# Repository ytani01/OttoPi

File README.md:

# OttoPi: Otto DIY like biped robot for Raspberry Pi

see [github pages](https://ytani01.github.io/OttoPi/)

## Power ON/OFF Button

### Power ON button

GPIO 3 -> SW -> GND

### Shutdown button

GPIO 4 -> SW -> GND
GPIO 21 -> R(1K ohm) -> LED -> GND

```
dtoverlay=gpio-shutdown,gpio_pin=4
dtoverlay=gpio-poweroff,gpiopin=21,active_low=1
```

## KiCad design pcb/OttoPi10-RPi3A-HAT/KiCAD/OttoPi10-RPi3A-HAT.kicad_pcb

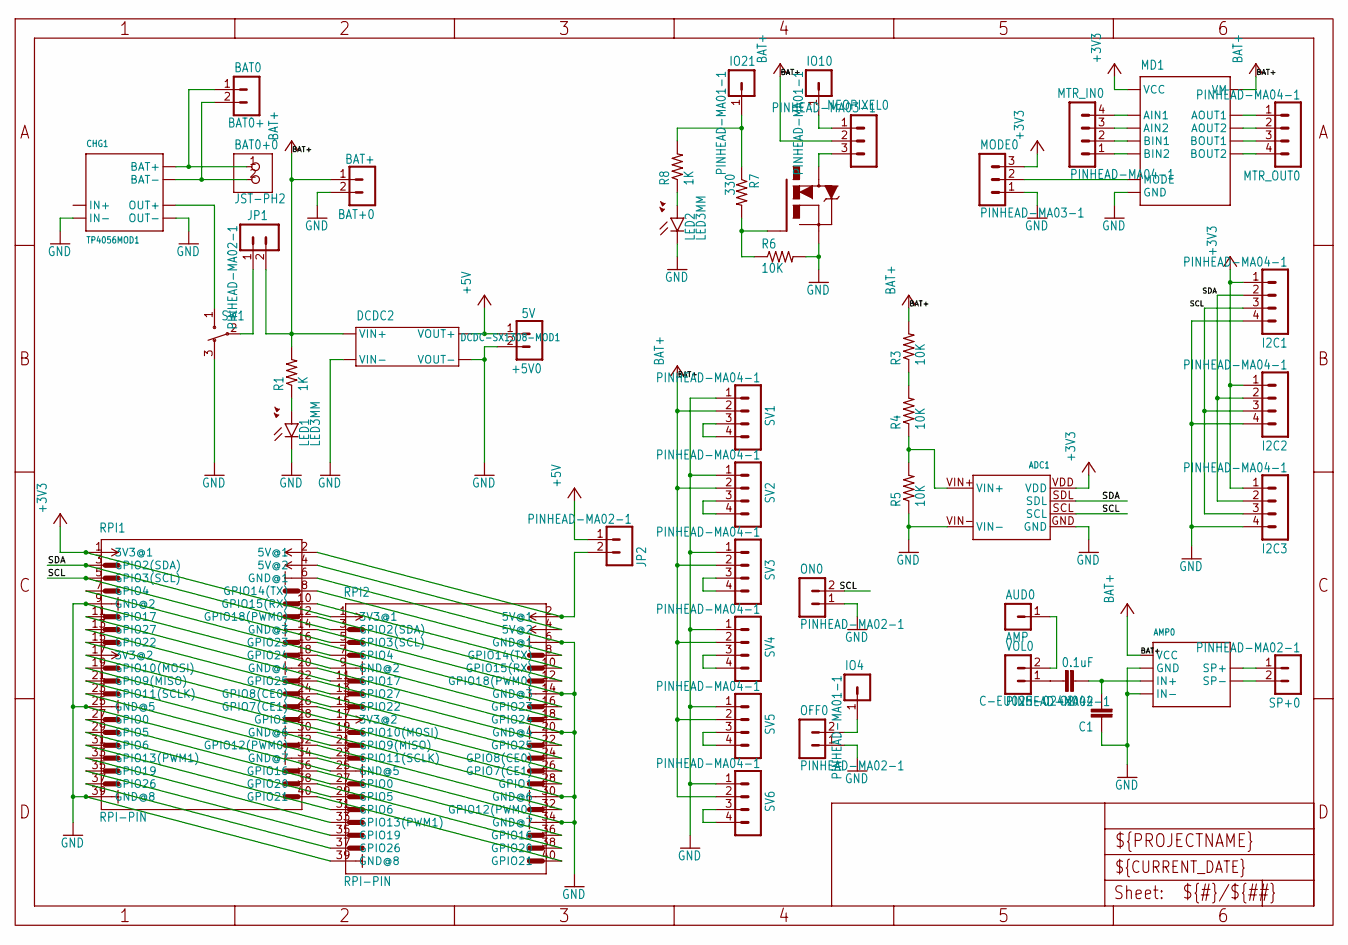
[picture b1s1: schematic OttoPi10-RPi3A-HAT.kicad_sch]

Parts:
+5V0: 5V; PINHEAD-MA02-1
ADC1: MCP3425MOD
AMP0: AMP; PAM8012MOD-A
AUD0: AMP; PINHEAD-MA01-1
BAT0: BAT0+; PINHEAD-MA02-1
BAT0+0: JST-PH2
BAT+0: BAT+; PINHEAD-MA02-1
C1: C-EU025-024X044; C025-024X044
C2: 0.1uF; C025-024X044
CHG1: TP4056MOD1
DCDC2: DCDC-SX1308-MOD1
I2C1, I2C2, I2C3: PINHEAD-MA04-1
IO4, IO10, IO21: PINHEAD-MA01-1
JP1, JP2: PINHEAD-MA02-1
LED1, LED2: LED3MM
MD1: DRV8835MOD
MODE0: PINHEAD-MA03-1
MTR_IN0: PINHEAD-MA04-1
MTR_OUT0: PINHEAD-MA04-1
NEOPIXEL0: PINHEAD-MA03-1
OFF0: PINHEAD-MA02-1
ON0: PINHEAD-MA02-1
Q1: 2SK4017; MOSFET-1
R1, R8: 1K; 0204_7
R3, R4, R5, R6: 10K; 0204_7
R7: 330; 0204_7
RPI1, RPI2: RPI-PIN
SP+0: PINHEAD-MA02-1
SV1, SV2, SV3, SV4, SV5, SV6: PINHEAD-MA04-1
SW1: SW3-1
VOL0: PINHEAD-MA02-1

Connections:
+3V3: ADC1.VDD, I2C1.1, I2C2.1, I2C3.1, MD1.VCC, MODE0.3, RPI1.1 (3V3@1), RPI2.1 (3V3@1)
+5V: +5V0.1, DCDC2.VOUT+, JP2.1
AIN1: MD1.AIN1, MTR_IN0.4
AIN2: MD1.AIN2, MTR_IN0.3
AOUT1: MD1.AOUT1, MTR_OUT0.1
AOUT2: MD1.AOUT2, MTR_OUT0.2
AUDIO0: AUD0.1, VOL0.2
AUDIO1: AMP0.IN+, C1.2, C2.1
BAT+: AMP0.V+ (VCC), BAT+0.1, DCDC2.VIN+, JP1.2, MD1.VM, NEOPIXEL0.2, R1.2, R3.2, SV1.2, SV2.2, SV3.2, SV4.2, SV5.2, SV6.2
BAT+0: BAT0.1, BAT0+0.1, CHG1.BAT+
BAT+1: CHG1.OUT+, SW1.1
BAT+2: JP1.1, SW1.2
BAT-0: BAT0.2, BAT0+0.2, CHG1.BAT-
BIN1: MD1.BIN1, MTR_IN0.2
BIN2: MD1.BIN2, MTR_IN0.1
BOUT1: MD1.BOUT1, MTR_OUT0.3
BOUT2: MD1.BOUT2, MTR_OUT0.4
GND: +5V0.2, ADC1.GND, ADC1.VIN-, AMP0.GND, AMP0.IN-, BAT+0.2, C1.1, CHG1.IN-, CHG1.OUT-, DCDC2.VIN-, DCDC2.VOUT-, I2C1.4, I2C2.4, I2C3.4, LED1.K (C), LED2.K (C), MD1.GND, MODE0.1, OFF0.1, ON0.1, Q1.S, R5.1, R6.2, RPI1.6 (GND@1), RPI1.9 (GND@2), RPI1.14 (GND@3), RPI1.20 (GND@4), RPI1.25 (GND@5), RPI1.30 (GND@6), RPI1.34 (GND@7), RPI1.39 (GND@8), RPI2.6 (GND@1), RPI2.9 (GND@2), RPI2.14 (GND@3), RPI2.20 (GND@4), RPI2.25 (GND@5), RPI2.30 (GND@6), RPI2.34 (GND@7), RPI2.39 (GND@8), SV1.1, SV2.1, SV3.1, SV4.1, SV5.1, SV6.1, SW1.3
GPIO10: RPI1.17 (3V3@2), RPI2.17 (3V3@2)
MODE: MD1.MODE, MODE0.2
unnamed: Q1.G, R6.1, R7.2
unnamed: NEOPIXEL0.3, Q1.D
unnamed: LED1.A, R1.1
unnamed: IO21.1, R7.1, R8.2
unnamed: JP2.2, RPI1.2 (5V@1), RPI2.2 (5V@1)
unnamed: RPI1.7 (GPIO4), RPI2.7 (GPIO4)
unnamed: IO10.1, NEOPIXEL0.1
unnamed: RPI1.11 (GPIO17), RPI2.11 (GPIO17)
unnamed: RPI1.13 (GPIO27), RPI2.13 (GPIO27)
unnamed: RPI1.15 (GPIO22), RPI2.15 (GPIO22)
unnamed: RPI1.23 (GPIO11(SCLK)), RPI2.23 (GPIO11(SCLK))
unnamed: RPI1.19 (GPIO10(MOSI)), RPI2.19 (GPIO10(MOSI))
unnamed: RPI1.21 (GPIO9(MISO)), RPI2.21 (GPIO9(MISO))
unnamed: C2.2, VOL0.1
unnamed: RPI1.4 (5V@2), RPI2.4 (5V@2)
unnamed: LED2.A, R8.1
unnamed: RPI1.8 (GPIO14(TX)), RPI2.8 (GPIO14(TX))
unnamed: RPI1.10 (GPIO15(RX)), RPI2.10 (GPIO15(RX))
unnamed: RPI1.12 (GPIO18(PWM0)), RPI2.12 (GPIO18(PWM0))
unnamed: RPI1.16 (GPIO23), RPI2.16 (GPIO23)
unnamed: RPI1.18 (GPIO24), RPI2.18 (GPIO24)
unnamed: RPI1.22 (GPIO25), RPI2.22 (GPIO25)
unnamed: IO4.1, OFF0.2
unnamed: R3.1, R4.2
unnamed: ADC1.VIN+, R4.1, R5.2
unnamed: RPI1.24 (GPIO8(CE0)), RPI2.24 (GPIO8(CE0))
unnamed: RPI1.26 (GPIO7(CE1)), RPI2.26 (GPIO7(CE1))
unnamed: RPI1.27 (GPIO0), RPI2.27 (GPIO0)
unnamed: RPI1.28 (GPIO1), RPI2.28 (GPIO1)
unnamed: RPI1.29 (GPIO5), RPI2.29 (GPIO5)
unnamed: RPI1.31 (GPIO6), RPI2.31 (GPIO6)
unnamed: RPI1.32 (GPIO12(PWM0)), RPI2.32 (GPIO12(PWM0))
unnamed: RPI1.33 (GPIO13(PWM1)), RPI2.33 (GPIO13(PWM1))
unnamed: RPI1.35 (GPIO19), RPI2.35 (GPIO19)
unnamed: RPI1.36 (GPIO16), RPI2.36 (GPIO16)
unnamed: RPI1.37 (GPIO26), RPI2.37 (GPIO26)
unnamed: RPI1.38 (GPIO20), RPI2.38 (GPIO20)
unnamed: RPI1.40 (GPIO21), RPI2.40 (GPIO21)
unnamed: SV2.3, SV2.4
unnamed: SV3.3, SV3.4
unnamed: SV4.3, SV4.4
unnamed: SV1.3, SV1.4
unnamed: SV5.3, SV5.4
unnamed: SV6.3, SV6.4
SCL: ADC1.SCL, I2C1.3, I2C2.3, I2C3.3, ON0.2, RPI1.5 (GPIO3(SCL)), RPI2.5 (GPIO3(SCL))
SDA: ADC1.SDL, I2C1.2, I2C2.2, I2C3.2, RPI1.3 (GPIO2(SDA)), RPI2.3 (GPIO2(SDA))
SP+: AMP0.SP+@1 (SP+), SP+0.1
SP-: AMP0.SP-@1 (SP-), SP+0.2

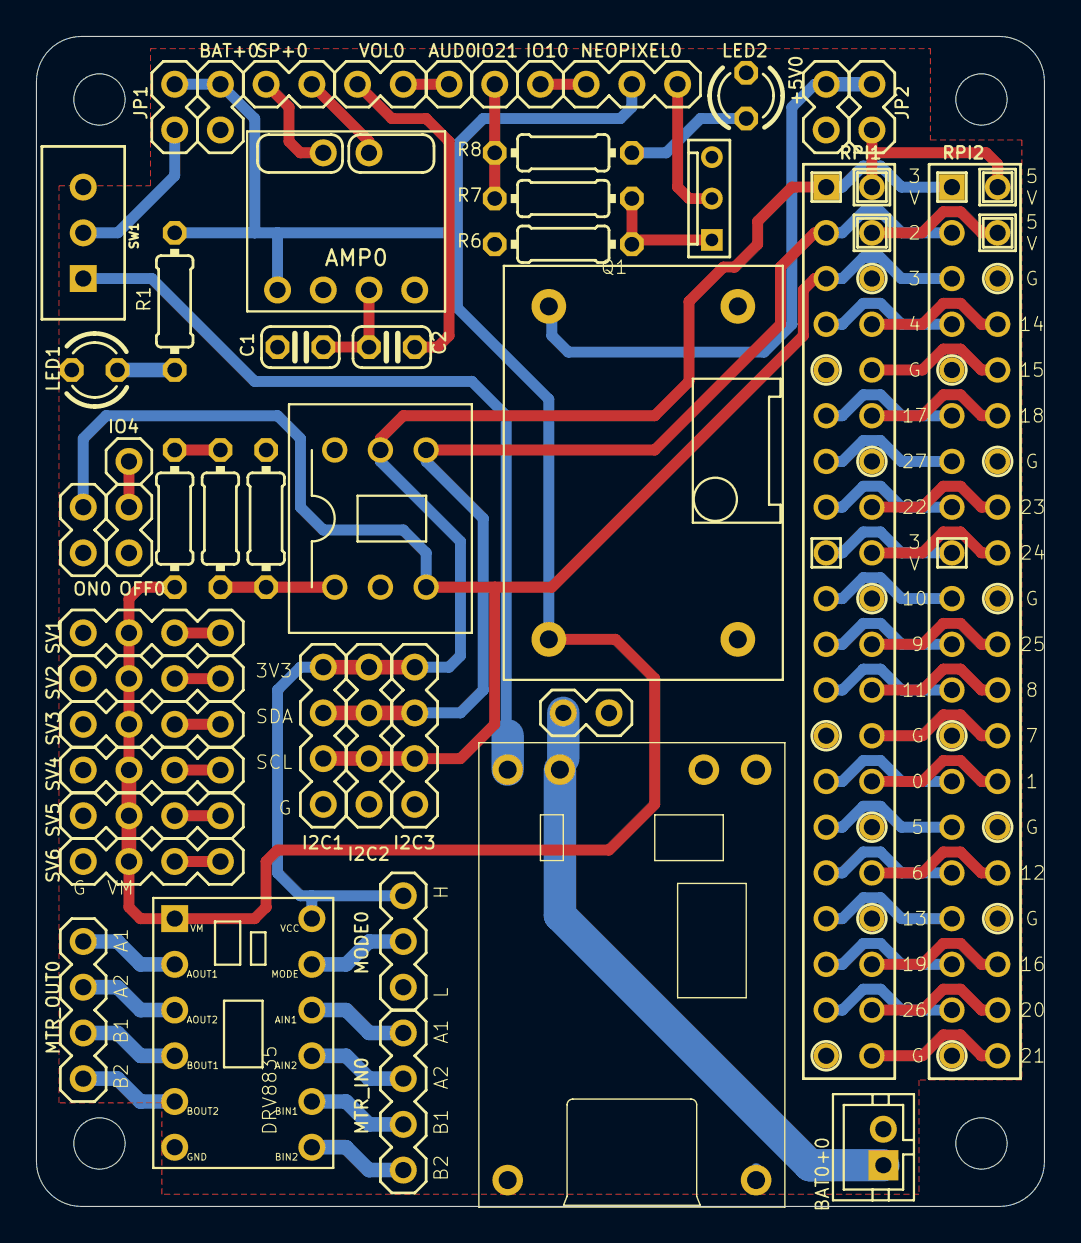
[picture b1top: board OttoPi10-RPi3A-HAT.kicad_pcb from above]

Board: 2 copper layers, 56.0 x 65.0 mm, 51 parts (0 on the bottom side), 68 nets.

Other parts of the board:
UNK_HOLE_0: dummyfp0
UNK_HOLE_1: dummyfp1
UNK_HOLE_2: dummyfp2
UNK_HOLE_3: dummyfp3

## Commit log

2019-05-07 OttoPi.py
2019-05-09 OttoPiCtrl.py
2019-05-10 side*()
2019-05-11 OttoPiServer.py
2019-05-11 README.md
2019-05-12 pipenv
2019-05-14 HTTP Server
2019-09-25 OttoPi-01.fzz
2019-11-08 init.el
2019-11-11 sound
2020-01-06 Set theme jekyll-theme-cayman
2020-03-07 websockets
2020-03-20 BleServer
2020-03-25 bug fix
2020-03-30 Set theme jekyll-theme-leap-day
2020-04-05 ble_observer.ino
2020-09-04 update pcb
2020-09-09 pcb/OttoPi04
2020-09-14 pcb/OttoPi04-RPiZeroHAT
2020-10-13 docs
2020-10-13 Set theme jekyll-theme-minimal
2020-10-23 OttoPi-Web1.png
2020-11-02 body
2020-11-05 music
2020-12-28 [update] PCB
2021-01-27 Youtube link
2021-06-12 [add] media/
2021-07-01 UPDATE: SPEECH_INTERVAL=120
2021-09-04 UPD: docs/index.md
2021-09-21 ADD: pcb/OttoPi08-RPi3AHAT
2021-09-22 UPD: pcb/OttoPi08-RPi3AHAT
2021-09-27 ADD: pcb/OttoPi09-RPi3A-HAT
2021-09-30 UPD: pcb
2021-10-01 UPD: README.md
2021-10-03 UPD: music
2021-11-01 UPD: hi_right, hi_left, bye_right, bye_left
2021-11-01 ADD: dance.py
2021-11-02 UPD: Motion
2021-11-02 UPD: OttoPiMotion.py
2021-11-02 UPD: Dance mode
2021-11-04 UPD: OttoPiMotion.py dance.py etc.
2021-11-04 UPD: index.html
2021-11-05 UPD: update
2021-11-05 UPD: dance
2021-11-13 ADD: dance2
2021-11-13 UPD: OttoPiMotion PiServo
2022-06-13 ADD: ScratchLink/
2022-06-13 ADD: junk file
2022-06-13 DEL: junk
2023-02-20 ADD: pcb/OttoPi10-
2023-05-31 zero01
2023-06-01 PiServo.py
2025-03-08 ADD: pcb/.../KiCAD/
2025-11-12 ADD: pcb/OttoPi10-Rpi3A-HAT/..
